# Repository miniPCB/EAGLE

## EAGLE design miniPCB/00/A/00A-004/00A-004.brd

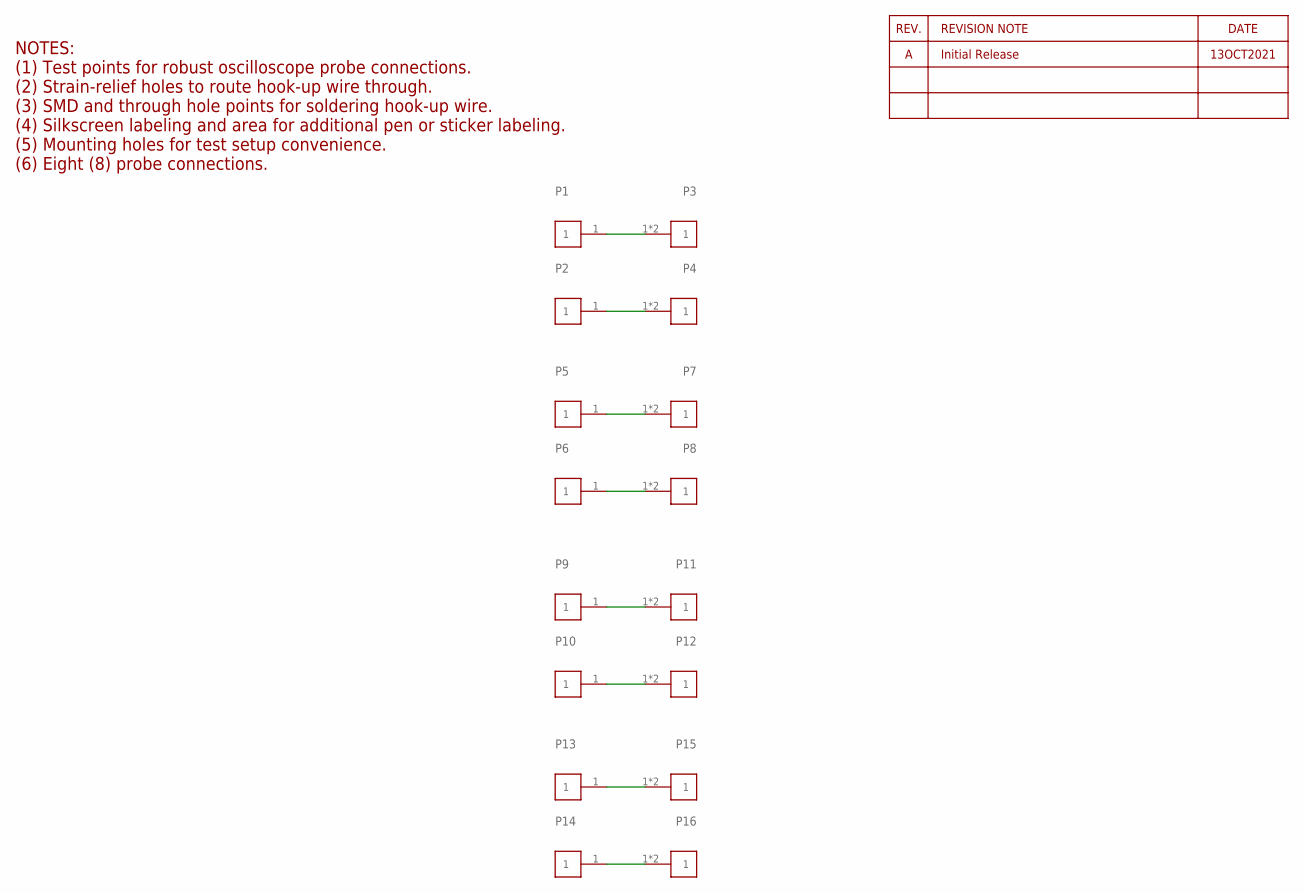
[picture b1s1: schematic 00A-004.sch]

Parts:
P1, P2, P5, P6, P9, P10, P13, P14: PINS_1KE_5000; PINS_1_TESTPOINT_KE5000
P3, P4, P7, P8, P11, P12, P15, P16: PINS_124AWG; PINS_1_1MM

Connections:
unnamed: P1.1, P3.1, P3.2
unnamed: P2.1, P4.1, P4.2
unnamed: P5.1, P7.1, P7.2
unnamed: P6.1, P8.1, P8.2
unnamed: P9.1, P11.1, P11.2
unnamed: P10.1, P12.1, P12.2
unnamed: P13.1, P15.1, P15.2
unnamed: P14.1, P16.1, P16.2

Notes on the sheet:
NOTES: (1) Test points for robust oscilloscope probe connections. (2) Strain-relief holes to route hook-up wire through. (3) SMD and through hole points for soldering hook-up wire. (4) Silkscreen labeling and area for additional pen or sticker labeling. (5) Mounting holes for test setup convenience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
13OCT2021

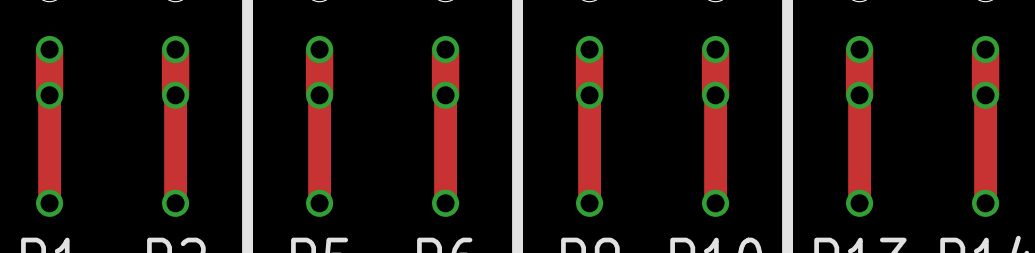
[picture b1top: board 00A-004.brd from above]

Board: 2 copper layers, 17 parts (0 on the bottom side), 8 nets.

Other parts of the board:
U$1: MINIPCB-LOGO

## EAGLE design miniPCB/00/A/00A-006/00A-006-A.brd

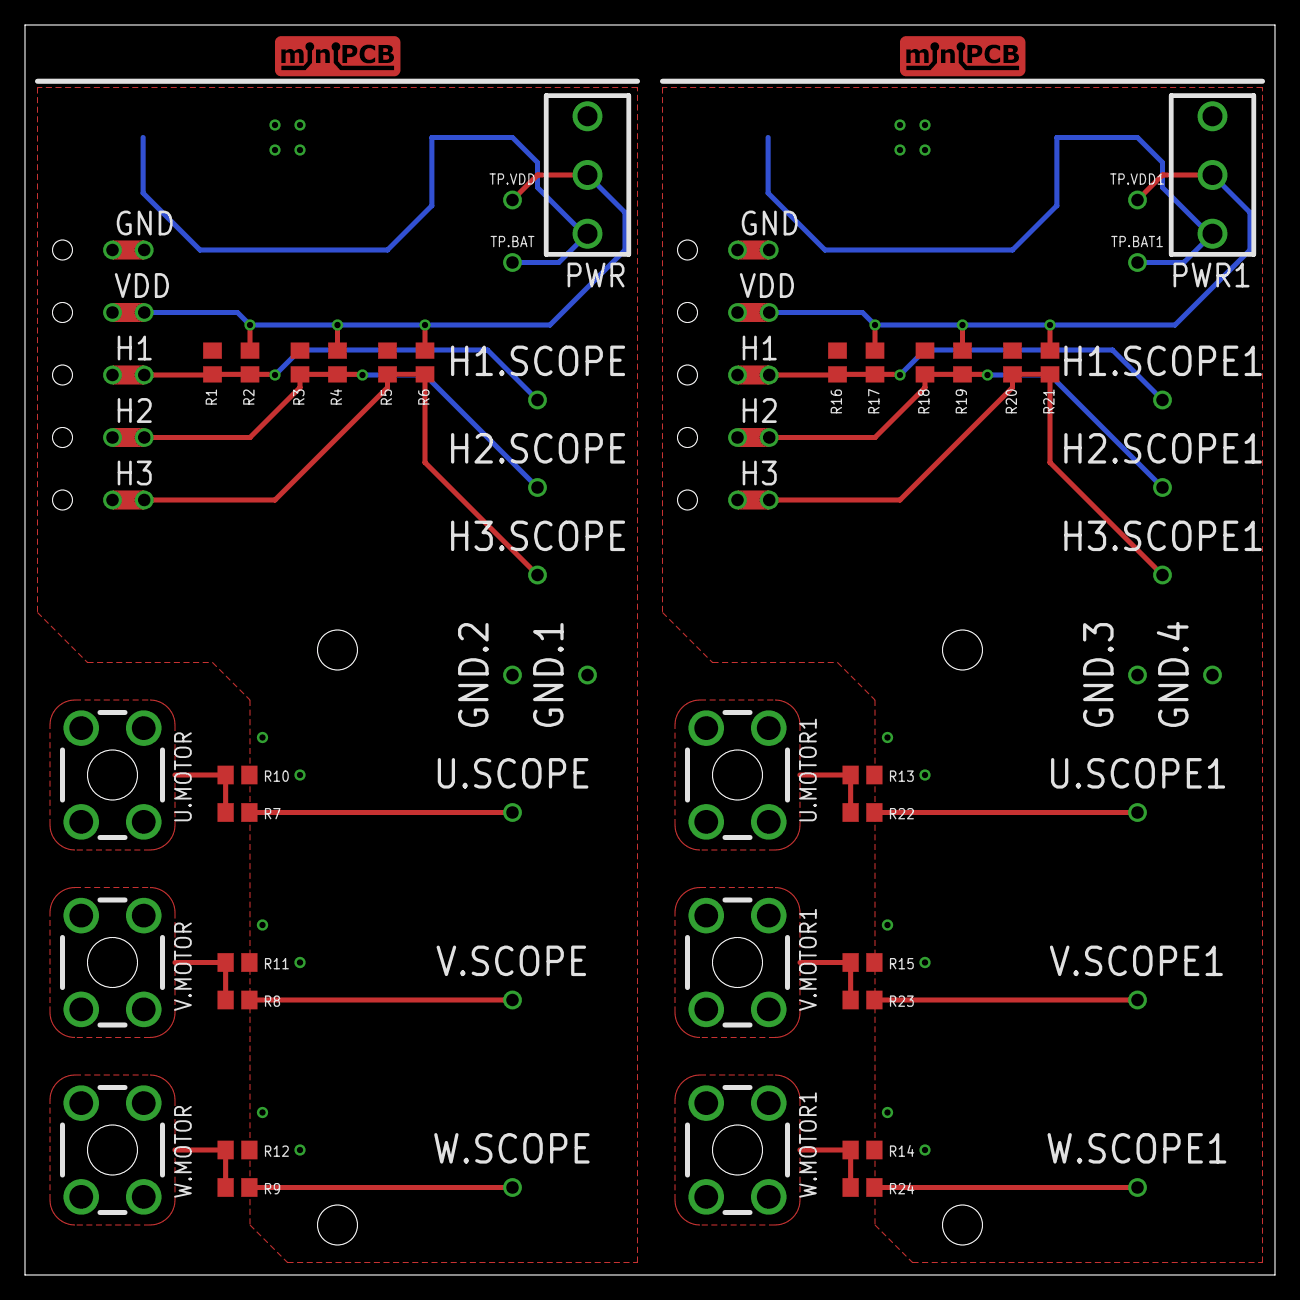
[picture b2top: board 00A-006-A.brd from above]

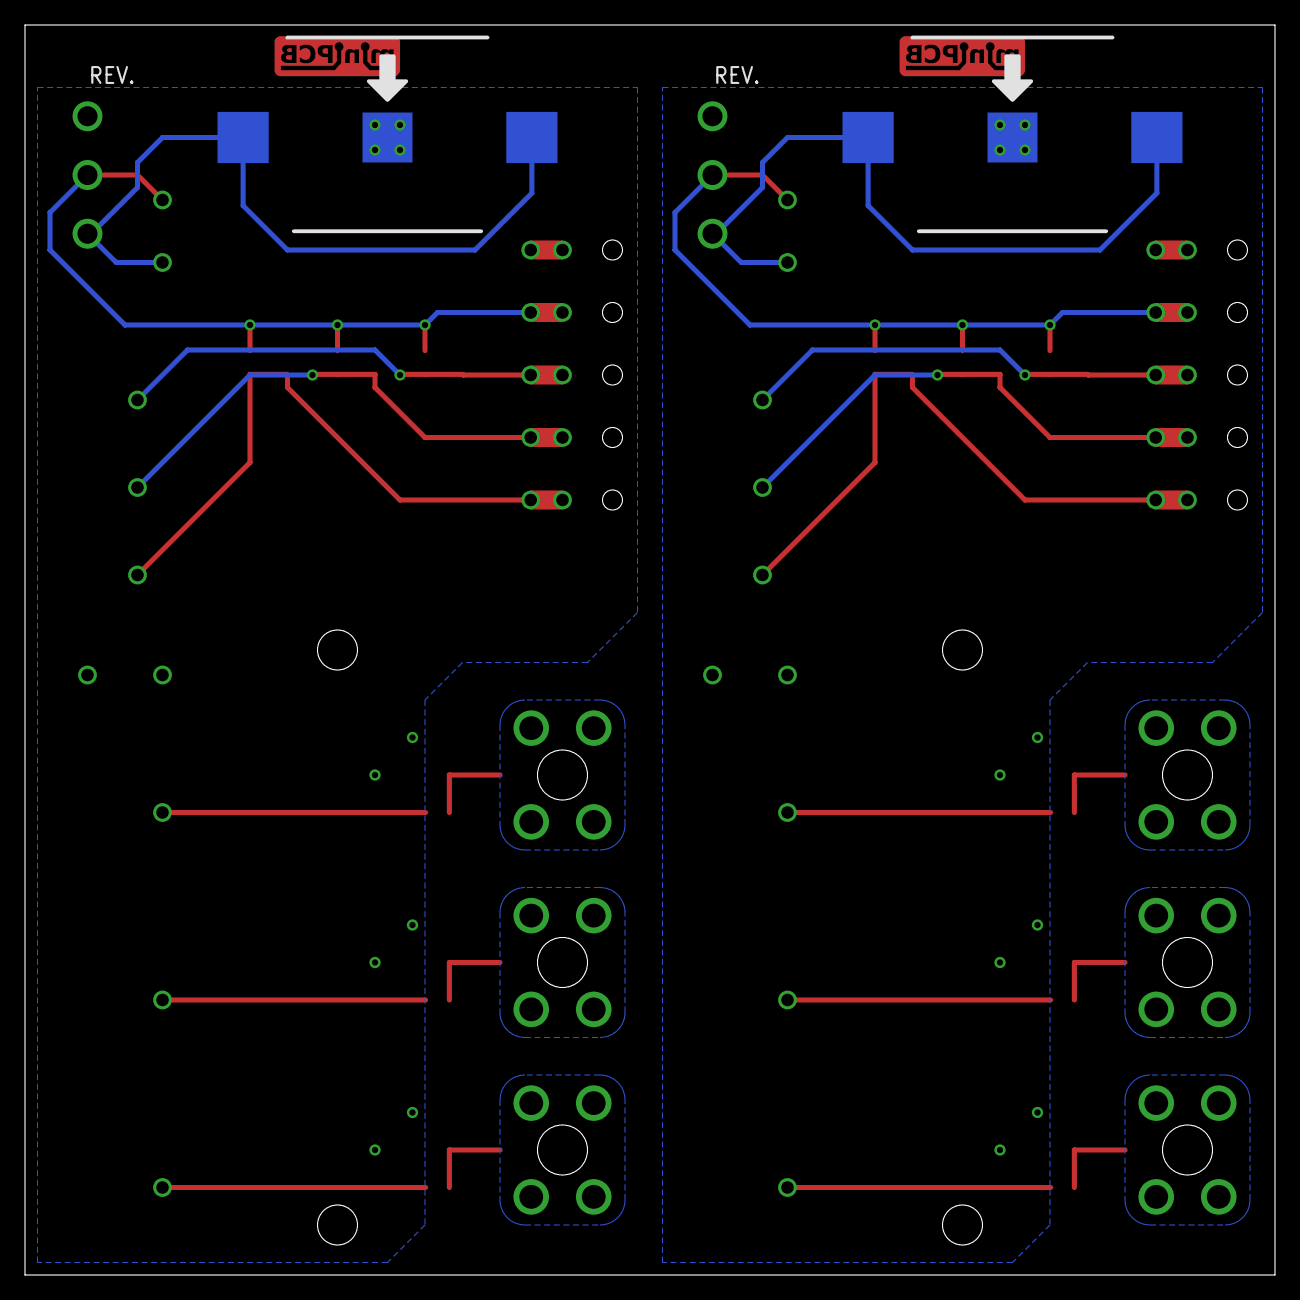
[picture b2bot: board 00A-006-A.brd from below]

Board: 2 copper layers, 100.0 x 100.0 mm, 66 parts (2 on the bottom side), 24 nets.

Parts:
B1, B2: CR3032; BATTERY-CR3032-KE3034
GND.1, GND.4: PINS_1_TESTPOINT_KE5000
GND.2, GND.3: TESTPOINTKE5000; PINS_1_TESTPOINT_KE5000
H1.SCOPE, H1.SCOPE1, H2.SCOPE, H2.SCOPE1, H3.SCOPE, H3.SCOPE1: PINS_1_TESTPOINT_KE5000
H1.SENSOR, H1.SENSOR1: H1; PINS_1_1MM
H2.SENSOR, H2.SENSOR1: H2; PINS_1_1MM
H3.SENSOR, H3.SENSOR1: H3; PINS_1_1MM
H.GND, H.GND1: GND; PINS_1_1MM
H.VDD, H.VDD1: VDD; PINS_1_1MM
PWR, PWR1: CK1101
R1, R2, R3, R4, R5, R6, R16, R17, R18, R19, R20, R21: 2k2; R0805
R7, R8, R9, R10, R11, R12, R13, R14, R15, R22, R23, R24: 220k; R0805
TP.BAT, TP.BAT1, TP.VDD, TP.VDD1: TESTPOINTKE5000-SMTEXT; PINS_1_TESTPOINT_KE5000_NOTEXT
U$1, U$2: MINIPCB_0P50X100; MINIPCB_0P_50X100
U.MOTOR, U.MOTOR1: SCREW-TERMINAL-M3
U.SCOPE, U.SCOPE1: PINS_1_TESTPOINT_KE5000
V.MOTOR, V.MOTOR1: SCREW-TERMINAL-M3
V.SCOPE, V.SCOPE1: PINS_1_TESTPOINT_KE5000
W.MOTOR, W.MOTOR1: SCREW-TERMINAL-M3
W.SCOPE, W.SCOPE1: PINS_1_TESTPOINT_KE5000

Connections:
GND: B1.3-, GND.1.1, GND.2.1, H.GND.1, H.GND.2, R1.1, R3.1, R5.1, R10.2, R11.2, R12.2
GND1: B2.3-, GND.3.1, GND.4.1, H.GND1.1, H.GND1.2, R13.2, R14.2, R15.2, R16.1, R18.1, R20.1
H1: H1.SCOPE.1, H1.SENSOR.1, H1.SENSOR.2, R1.2, R2.2
H2: H2.SCOPE.1, H2.SENSOR.1, H2.SENSOR.2, R3.2, R4.2
H3: H3.SCOPE.1, H3.SENSOR.1, H3.SENSOR.2, R5.2, R6.2
H4: H1.SCOPE1.1, H1.SENSOR1.1, H1.SENSOR1.2, R16.2, R17.2
H5: H2.SCOPE1.1, H2.SENSOR1.1, H2.SENSOR1.2, R18.2, R19.2
H6: H3.SCOPE1.1, H3.SENSOR1.1, H3.SENSOR1.2, R20.2, R21.2
HVDD: H.VDD.1, H.VDD.2, PWR.P$2, R2.1, R4.1, R6.1, TP.VDD.1
HVDD1: H.VDD1.1, H.VDD1.2, PWR1.P$2, R17.1, R19.1, R21.1, TP.VDD1.1
U.MOTOR: R7.1, R10.1, U.MOTOR.1, U.MOTOR.2, U.MOTOR.3, U.MOTOR.4
U.MOTOR1: R13.1, R22.1, U.MOTOR1.1, U.MOTOR1.2, U.MOTOR1.3, U.MOTOR1.4
U.SCOPE: R7.2, U.SCOPE.1
U.SCOPE1: R22.2, U.SCOPE1.1
V.BAT: B1.1+, B1.2+, PWR.P$1, TP.BAT.1
V.BAT1: B2.1+, B2.2+, PWR1.P$1, TP.BAT1.1
V.MOTOR: R8.1, R11.1, V.MOTOR.1, V.MOTOR.2, V.MOTOR.3, V.MOTOR.4
V.MOTOR1: R15.1, R23.1, V.MOTOR1.1, V.MOTOR1.2, V.MOTOR1.3, V.MOTOR1.4
V.SCOPE: R8.2, V.SCOPE.1
V.SCOPE1: R23.2, V.SCOPE1.1
W.MOTOR: R9.1, R12.1, W.MOTOR.1, W.MOTOR.2, W.MOTOR.3, W.MOTOR.4
W.MOTOR1: R14.1, R24.1, W.MOTOR1.1, W.MOTOR1.2, W.MOTOR1.3, W.MOTOR1.4
W.SCOPE: R9.2, W.SCOPE.1
W.SCOPE1: R24.2, W.SCOPE1.1

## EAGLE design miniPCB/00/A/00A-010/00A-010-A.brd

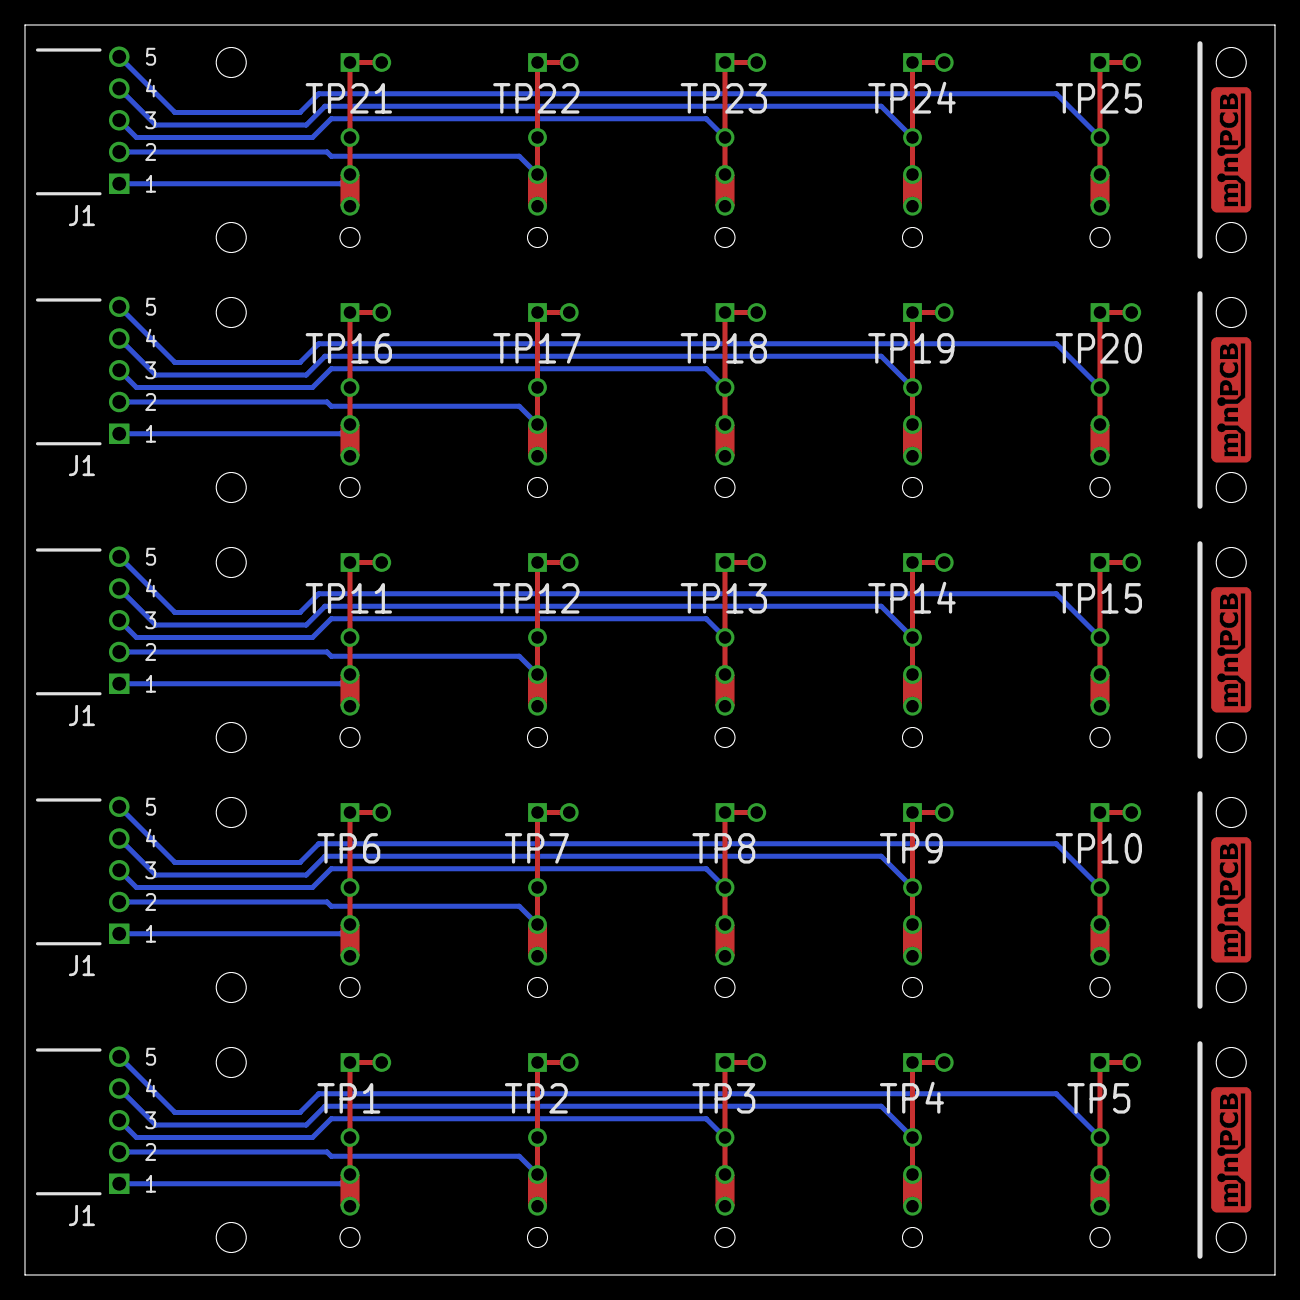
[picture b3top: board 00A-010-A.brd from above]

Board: 2 copper layers, 100.0 x 100.0 mm, 81 parts (0 on the bottom side), 25 nets.

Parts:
E$1: MINPCB_PANEL_IMAGEFRAME
J1, J2, J3, J4, J5: MINIPCB_IDB20-X-05
P1, P2, P3, P4, P5, P11, P12, P13, P14, P15, P21, P22, P23, P24, P25, P31, P32, P33, P34, P35, P41, P42, P43, P44, P45: PINS_2_NOTEXT
P6, P7, P8, P9, P10, P16, P17, P18, P19, P20, P26, P27, P28, P29, P30, P36, P37, P38, P39, P40, P46, P47, P48, P49, P50: PINS_1_1MM_K
TP1, TP2, TP3, TP4, TP5, TP6, TP7, TP8, TP9, TP10, TP11, TP12, TP13, TP14, TP15, TP16, TP17, TP18, TP19, TP20, TP21, TP22, TP23, TP24, TP25: PINS_1_TESTPOINT_KE5000

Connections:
unnamed: J1.2, P2.1, P2.2, P7.1, P7.2, TP2.1
unnamed: J1.1, P1.1, P1.2, P6.1, P6.2, TP1.1
unnamed: J1.3, P3.1, P3.2, P8.1, P8.2, TP3.1
unnamed: J1.4, P4.1, P4.2, P9.1, P9.2, TP4.1
unnamed: J1.5, P5.1, P5.2, P10.1, P10.2, TP5.1
unnamed: J2.2, P12.1, P12.2, P17.1, P17.2, TP7.1
unnamed: J2.1, P11.1, P11.2, P16.1, P16.2, TP6.1
unnamed: J2.3, P13.1, P13.2, P18.1, P18.2, TP8.1
unnamed: J2.4, P14.1, P14.2, P19.1, P19.2, TP9.1
unnamed: J2.5, P15.1, P15.2, P20.1, P20.2, TP10.1
unnamed: J3.2, P22.1, P22.2, P27.1, P27.2, TP12.1
unnamed: J3.1, P21.1, P21.2, P26.1, P26.2, TP11.1
unnamed: J3.3, P23.1, P23.2, P28.1, P28.2, TP13.1
unnamed: J3.4, P24.1, P24.2, P29.1, P29.2, TP14.1
unnamed: J3.5, P25.1, P25.2, P30.1, P30.2, TP15.1
unnamed: J4.2, P32.1, P32.2, P37.1, P37.2, TP17.1
unnamed: J4.1, P31.1, P31.2, P36.1, P36.2, TP16.1
unnamed: J4.3, P33.1, P33.2, P38.1, P38.2, TP18.1
unnamed: J4.4, P34.1, P34.2, P39.1, P39.2, TP19.1
unnamed: J4.5, P35.1, P35.2, P40.1, P40.2, TP20.1
unnamed: J5.2, P42.1, P42.2, P47.1, P47.2, TP22.1
unnamed: J5.1, P41.1, P41.2, P46.1, P46.2, TP21.1
unnamed: J5.3, P43.1, P43.2, P48.1, P48.2, TP23.1
unnamed: J5.4, P44.1, P44.2, P49.1, P49.2, TP24.1
unnamed: J5.5, P45.1, P45.2, P50.1, P50.2, TP25.1

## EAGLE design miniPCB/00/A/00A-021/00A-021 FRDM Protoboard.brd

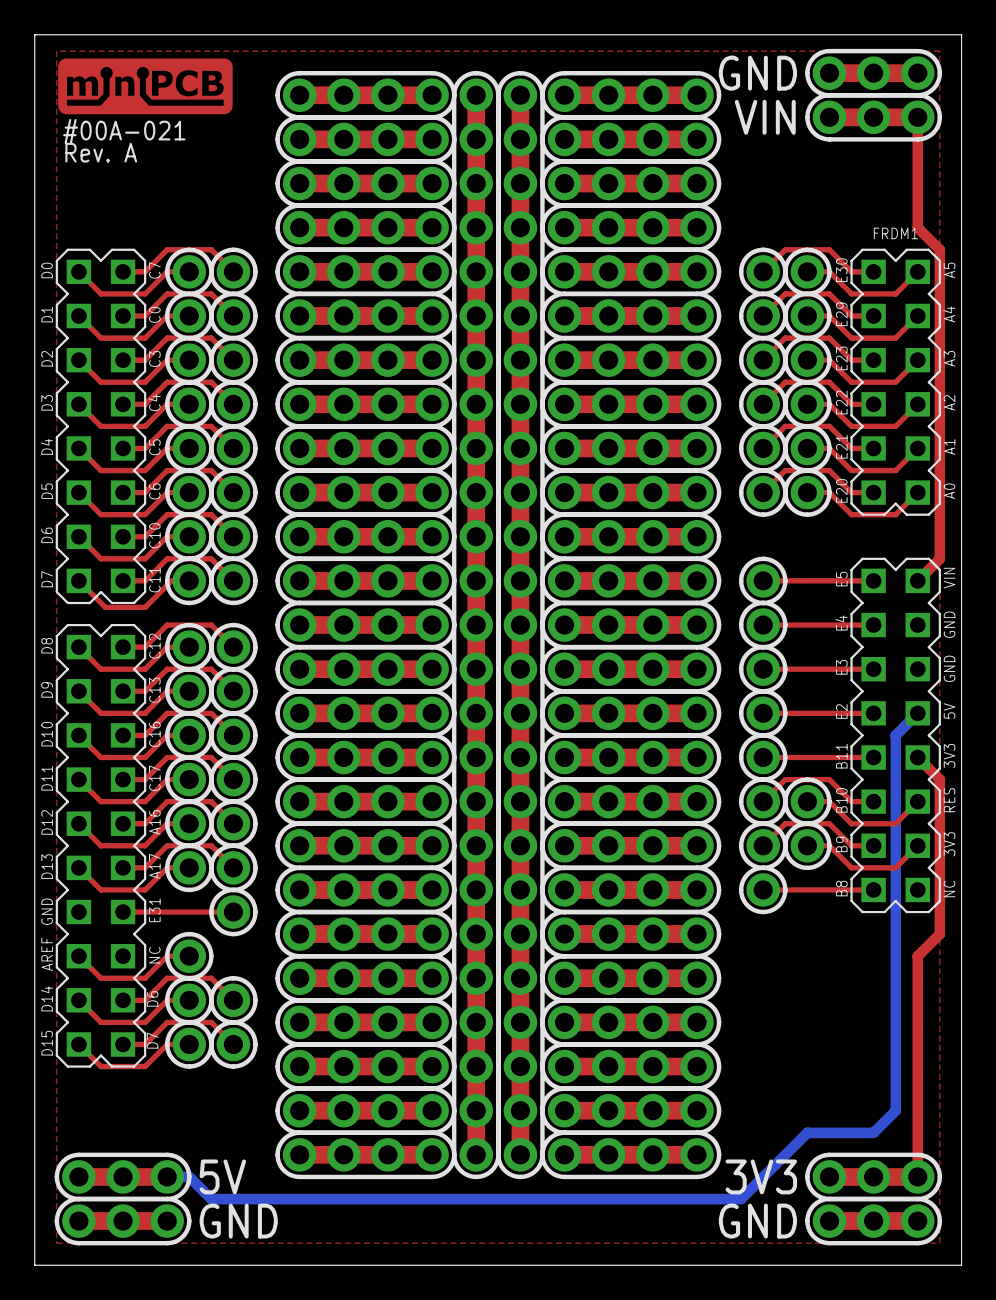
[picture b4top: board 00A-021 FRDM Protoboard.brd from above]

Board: 2 copper layers, 53.3 x 70.8 mm, 116 parts (0 on the bottom side), 60 nets.

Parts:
FRDM1: FRDM-KL25ZNORMAL; FRDM_KL25Z_NORMAL
P1, P2, P3, P4, P5, P6, P7, P8, P9, P10, P11, P12, P13, P14, P15, P16, P17, P18, P19, P20, P21, P22, P23, P24, P25, P26, P27, P28, P29, P30, P31, P32, P33, P34, P35, P36, P37, P38, P39, P40, P41, P42, P43, P44, P45, P46, P47, P48, P49, P50, P51, P52, P53, P54, P55, P56: PINS_1-1P_VALUE
P57: 3V3; PINS_1-3P_VALUE
P58: 5V; PINS_1-3P_VALUE
P59: VIN; PINS_1-3P_VALUE
P60, P61, P62, P63, P64, P65, P66, P67, P68, P69, P70, P71, P72, P73, P74, P75, P76, P77, P78, P79, P82, P83, P84, P85, P86, P87, P88, P89, P90, P91, P92, P93, P94, P95, P96, P97, P98, P99, P100, P101, P104, P105, P106, P107, P108, P109, P110, P111, P112, P113: PINS_1_4P_VALUE
P80, P81: PINS_1_25P_VALUE
P102, P103, P114: GND; PINS_1-3P_VALUE
U$1: MINIPCB_LOGO; MINIPCB-LOGO

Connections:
GND: FRDM1.GND0, FRDM1.GND1, FRDM1.GND2, P102.1, P102.2, P102.3, P103.1, P103.2, P103.3, P114.1, P114.2, P114.3
unnamed: FRDM1.PTB8, P1.1
unnamed: FRDM1.PTB9, P2.1
unnamed: FRDM1.PTB10, P3.1
unnamed: FRDM1.PTB11, P4.1
unnamed: FRDM1.PTE2, P5.1
unnamed: FRDM1.PTE3, P6.1
unnamed: FRDM1.PTE4, P7.1
unnamed: FRDM1.PTE5, P8.1
unnamed: FRDM1.A0, P9.1
unnamed: FRDM1.A1, P10.1
unnamed: FRDM1.A2, P11.1
unnamed: FRDM1.A3, P12.1
unnamed: FRDM1.A4, P13.1
unnamed: FRDM1.A5, P14.1
unnamed: FRDM1.PTE20, P15.1
unnamed: FRDM1.PTE21, P16.1
unnamed: FRDM1.PTE22, P17.1
unnamed: FRDM1.PTE23, P18.1
unnamed: FRDM1.PTE29, P19.1
unnamed: FRDM1.PTE30, P20.1
unnamed: FRDM1.PTD7, P21.1
unnamed: FRDM1.PTD6, P22.1
unnamed: FRDM1.PTE31, P23.1
unnamed: FRDM1.PTA17, P24.1
unnamed: FRDM1.PTA16, P25.1
unnamed: FRDM1.PTC17, P26.1
unnamed: FRDM1.PTC16, P27.1
unnamed: FRDM1.PTC13, P28.1
unnamed: FRDM1.PTC12, P29.1
unnamed: FRDM1.D15, P30.1
unnamed: FRDM1.D14, P31.1
unnamed: FRDM1.AREF, P32.1
unnamed: FRDM1.D13, P33.1
unnamed: FRDM1.D12, P34.1
unnamed: FRDM1.D11, P35.1
unnamed: FRDM1.D10, P36.1
unnamed: FRDM1.D9, P37.1
unnamed: FRDM1.D8, P38.1
unnamed: FRDM1.PTC11, P39.1
unnamed: FRDM1.PTC10, P40.1
unnamed: FRDM1.PTC6, P41.1
unnamed: FRDM1.PTC5, P42.1
unnamed: FRDM1.PTC4, P43.1
unnamed: FRDM1.PTC3, P44.1
unnamed: FRDM1.PTC0, P45.1
unnamed: FRDM1.PTC7, P46.1
unnamed: FRDM1.D7, P47.1
unnamed: FRDM1.D6, P48.1
unnamed: FRDM1.D5, P49.1
unnamed: FRDM1.D4, P50.1
unnamed: FRDM1.D3, P51.1
unnamed: FRDM1.D2, P52.1
unnamed: FRDM1.D1, P53.1
unnamed: FRDM1.D0, P54.1
unnamed: FRDM1.3V3, P55.1
unnamed: FRDM1.RESET, P56.1
unnamed: FRDM1.P3V3, P57.1, P57.2, P57.3
unnamed: FRDM1.5V, P58.1, P58.2, P58.3
unnamed: FRDM1.VIN, P59.1, P59.2, P59.3
